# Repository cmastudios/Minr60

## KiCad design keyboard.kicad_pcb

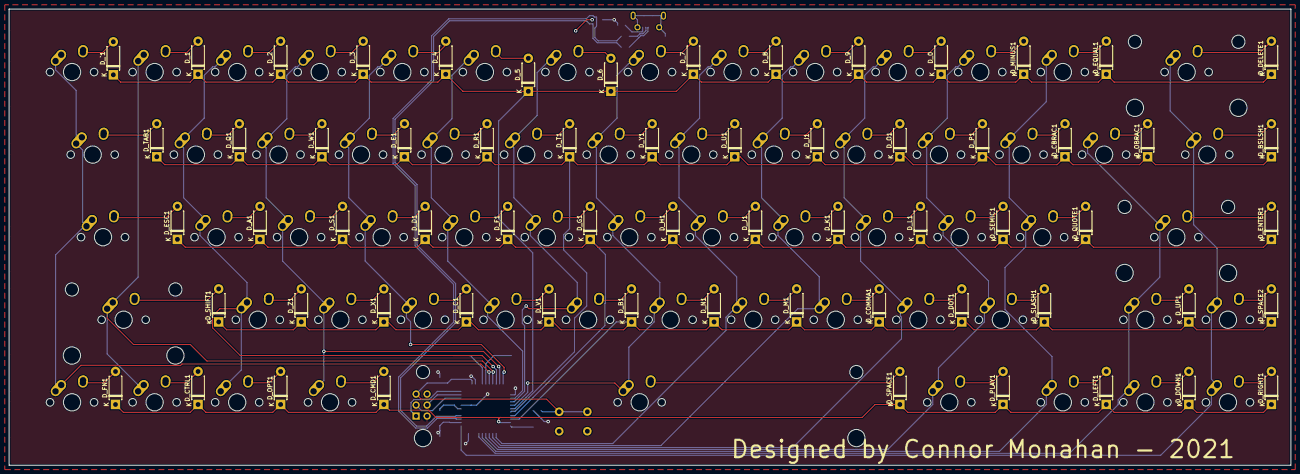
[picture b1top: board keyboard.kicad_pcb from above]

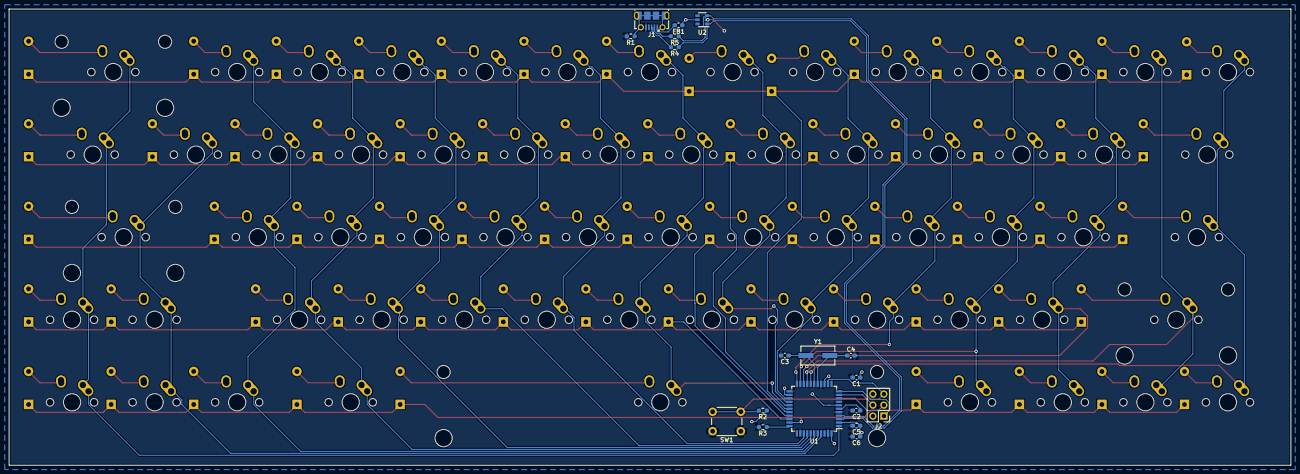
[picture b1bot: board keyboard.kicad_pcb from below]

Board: 2 copper layers, 295.8 x 105.2 mm, 144 parts (18 on the bottom side), 99 nets.

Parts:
C1: 10u; C_0603_1608Metric_Pad1.08x0.95mm_HandSolder
C2, C5: 1u; C_0603_1608Metric_Pad1.08x0.95mm_HandSolder
C3, C4: 22p; C_0603_1608Metric_Pad1.08x0.95mm_HandSolder
C6: 100n; C_0603_1608Metric_Pad1.08x0.95mm_HandSolder
D_0, D_1, D_2, D_3, D_4, D_5, D_6, D_7, D_8, D_9: D; D_DO-41_SOD81_P7.62mm_Horizontal
D_A1: D; D_DO-41_SOD81_P7.62mm_Horizontal
D_B1: D; D_DO-41_SOD81_P7.62mm_Horizontal
D_BSLSH1: D; D_DO-41_SOD81_P7.62mm_Horizontal
D_C1: D; D_DO-41_SOD81_P7.62mm_Horizontal
D_CBRAC1: D; D_DO-41_SOD81_P7.62mm_Horizontal
D_CMD1: D; D_DO-41_SOD81_P7.62mm_Horizontal
D_COMMA1: D; D_DO-41_SOD81_P7.62mm_Horizontal
D_CTRL1: D; D_DO-41_SOD81_P7.62mm_Horizontal
D_D1: D; D_DO-41_SOD81_P7.62mm_Horizontal
D_DELETE1: D; D_DO-41_SOD81_P7.62mm_Horizontal
D_DOT1: D; D_DO-41_SOD81_P7.62mm_Horizontal
D_DOWN1: D; D_DO-41_SOD81_P7.62mm_Horizontal
D_E1: D; D_DO-41_SOD81_P7.62mm_Horizontal
D_ENTER1: D; D_DO-41_SOD81_P7.62mm_Horizontal
D_EQUAL1: D; D_DO-41_SOD81_P7.62mm_Horizontal
D_ESC1: D; D_DO-41_SOD81_P7.62mm_Horizontal
D_F1: D; D_DO-41_SOD81_P7.62mm_Horizontal
D_FN1: D; D_DO-41_SOD81_P7.62mm_Horizontal
D_G1: D; D_DO-41_SOD81_P7.62mm_Horizontal
D_H1: D; D_DO-41_SOD81_P7.62mm_Horizontal
D_I1: D; D_DO-41_SOD81_P7.62mm_Horizontal
D_J1: D; D_DO-41_SOD81_P7.62mm_Horizontal
D_K1: D; D_DO-41_SOD81_P7.62mm_Horizontal
D_L1: D; D_DO-41_SOD81_P7.62mm_Horizontal
D_LEFT1: D; D_DO-41_SOD81_P7.62mm_Horizontal
D_M1: D; D_DO-41_SOD81_P7.62mm_Horizontal
D_MINUS1: D; D_DO-41_SOD81_P7.62mm_Horizontal
D_N1: D; D_DO-41_SOD81_P7.62mm_Horizontal
D_O1: D; D_DO-41_SOD81_P7.62mm_Horizontal
D_OBRAC1: D; D_DO-41_SOD81_P7.62mm_Horizontal
D_OPT1: D; D_DO-41_SOD81_P7.62mm_Horizontal
D_P1: D; D_DO-41_SOD81_P7.62mm_Horizontal
D_PLAY1: D; D_DO-41_SOD81_P7.62mm_Horizontal
D_Q1: D; D_DO-41_SOD81_P7.62mm_Horizontal
D_QUOTE1: D; D_DO-41_SOD81_P7.62mm_Horizontal
D_R1: D; D_DO-41_SOD81_P7.62mm_Horizontal
D_RIGHT1: D; D_DO-41_SOD81_P7.62mm_Horizontal
D_S1: D; D_DO-41_SOD81_P7.62mm_Horizontal
D_SEMIC1: D; D_DO-41_SOD81_P7.62mm_Horizontal
D_SHIFT1: D; D_DO-41_SOD81_P7.62mm_Horizontal
D_SLASH1: D; D_DO-41_SOD81_P7.62mm_Horizontal
D_SPACE1, D_SPACE2: D; D_DO-41_SOD81_P7.62mm_Horizontal
D_T1: D; D_DO-41_SOD81_P7.62mm_Horizontal
D_TAB1: D; D_DO-41_SOD81_P7.62mm_Horizontal
D_U1: D; D_DO-41_SOD81_P7.62mm_Horizontal
D_UP1: D; D_DO-41_SOD81_P7.62mm_Horizontal
D_V1: D; D_DO-41_SOD81_P7.62mm_Horizontal
D_W1: D; D_DO-41_SOD81_P7.62mm_Horizontal
D_X1: D; D_DO-41_SOD81_P7.62mm_Horizontal
D_Y1: D; D_DO-41_SOD81_P7.62mm_Horizontal
D_Z1: D; D_DO-41_SOD81_P7.62mm_Horizontal
D_`1: D; D_DO-41_SOD81_P7.62mm_Horizontal
FB1: Ferrite_Bead_Small; L_0603_1608Metric_Pad1.05x0.95mm_HandSolder
J1: USB_B_Micro; USB_Micro-B_Molex-105017-0001
J2: AVR-ISP-6; PinHeader_2x03_P2.54mm_Vertical
K_0, K_1, K_2, K_3, K_4, K_5, K_6, K_7, K_8, K_9: KEYSW; MX-1U-NoLED
K_A1: KEYSW; MX-1U-NoLED
K_B1: KEYSW; MX-1U-NoLED
K_BSLSH1: KEYSW; MX-1.5U-NoLED
K_C1: KEYSW; MX-1U-NoLED
K_CBRAC1: KEYSW; MX-1U-NoLED
K_CMD1: KEYSW; MX-1.25U-NoLED
K_COMMA1: KEYSW; MX-1U-NoLED
K_CTRL1: KEYSW; MX-1U-NoLED
K_D1: KEYSW; MX-1U-NoLED
K_DELETE1: KEYSW; MX-2U-NoLED
K_DOT1: KEYSW; MX-1U-NoLED
K_DOWN1: KEYSW; MX-1U-NoLED
K_E1: KEYSW; MX-1U-NoLED
K_ENTER1: KEYSW; MX-2.25U-NoLED
K_EQUAL1: KEYSW; MX-1U-NoLED
K_ESC1: KEYSW; MX-1.75U-NoLED
K_F1: KEYSW; MX-1U-NoLED
K_FN1: KEYSW; MX-1U-NoLED
K_G1: KEYSW; MX-1U-NoLED
K_H1: KEYSW; MX-1U-NoLED
K_I1: KEYSW; MX-1U-NoLED
K_J1: KEYSW; MX-1U-NoLED
K_K1: KEYSW; MX-1U-NoLED
K_L1: KEYSW; MX-1U-NoLED
K_LEFT1: KEYSW; MX-1U-NoLED
K_M1: KEYSW; MX-1U-NoLED
K_MINUS1: KEYSW; MX-1U-NoLED
K_N1: KEYSW; MX-1U-NoLED
K_O1: KEYSW; MX-1U-NoLED
K_OBRAC1: KEYSW; MX-1U-NoLED
K_OPT1: KEYSW; MX-1U-NoLED
K_P1: KEYSW; MX-1U-NoLED
K_PLAY1: KEYSW; MX-1.25U-NoLED
K_Q1: KEYSW; MX-1U-NoLED
K_QUOTE1: KEYSW; MX-1U-NoLED
K_R1: KEYSW; MX-1U-NoLED
K_RIGHT1: KEYSW; MX-1U-NoLED
K_S1: KEYSW; MX-1U-NoLED
K_SEMIC1: KEYSW; MX-1U-NoLED
K_SHIFT1: KEYSW; MX-2.25U-NoLED
K_SLASH1: KEYSW; MX-1U-NoLED
K_SPACE1: KEYSW; MX-6.25U-NoLED
K_SPACE2: KEYSW; MX-1U-NoLED
K_T1: KEYSW; MX-1U-NoLED
K_TAB1: KEYSW; MX-1.5U-NoLED
K_U1: KEYSW; MX-1U-NoLED
K_UP1: KEYSW; MX-1U-NoLED
K_V1: KEYSW; MX-1U-NoLED
K_W1: KEYSW; MX-1U-NoLED
K_X1: KEYSW; MX-1U-NoLED
K_Y1: KEYSW; MX-1U-NoLED
K_Z1: KEYSW; MX-1U-NoLED
K_`1: KEYSW; MX-1U-NoLED
R1: 1M; R_0603_1608Metric_Pad0.98x0.95mm_HandSolder
R2, R3: 10k; R_0603_1608Metric_Pad0.98x0.95mm_HandSolder
R4, R5: 22; R_0603_1608Metric_Pad0.98x0.95mm_HandSolder
SW1: SW_Push; SW_PUSH_6mm
U1: ATmega32U4-AU; TQFP-44_10x10mm_P0.8mm
U2: USBLC6-4SC6; SOT-23-6
Y1: 16MHz; Crystal_SMD_ECS_CSM3X-2Pin_7.6x4.1mm

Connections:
/DB+: J1.3, R4.2
/DB-: J1.2, R5.2
D+: R4.1, U1.4, U2.1
D-: R5.1, U1.3, U2.3
GND: C1.2, C2.2, C3.2, C4.2, C5.2, C6.2, J1.5, J2.6, R1.2, R3.2, SW1.1, U1.5, U1.15, U1.23, U1.35, U1.43, U2.2
MISO: J2.1, U1.11
MOSI: J2.4, U1.10
unnamed: C2.1, U1.6
unnamed: C3.1, U1.17, Y1.1
unnamed: C4.1, U1.16, Y1.2
unnamed: D_0.2, K_0.2
unnamed: D_1.2, K_1.2
unnamed: D_2.2, K_2.2
unnamed: D_3.2, K_3.2
unnamed: D_4.2, K_4.2
unnamed: D_5.2, K_5.2
unnamed: D_6.2, K_6.2
unnamed: D_7.2, K_7.2
unnamed: D_8.2, K_8.2
unnamed: D_9.2, K_9.2
unnamed: D_A1.2, K_A1.2
unnamed: D_B1.2, K_B1.2
unnamed: D_BSLSH1.2, K_BSLSH1.2
unnamed: D_C1.2, K_C1.2
unnamed: D_CBRAC1.2, K_CBRAC1.2
unnamed: D_CMD1.2, K_CMD1.2
unnamed: D_COMMA1.2, K_COMMA1.2
unnamed: D_CTRL1.2, K_CTRL1.2
unnamed: D_D1.2, K_D1.2
unnamed: D_DELETE1.2, K_DELETE1.2
unnamed: D_DOT1.2, K_DOT1.2
unnamed: D_DOWN1.2, K_DOWN1.2
unnamed: D_E1.2, K_E1.2
unnamed: D_ENTER1.2, K_ENTER1.2
unnamed: D_EQUAL1.2, K_EQUAL1.2
unnamed: D_ESC1.2, K_ESC1.2
unnamed: D_F1.2, K_F1.2
unnamed: D_FN1.2, K_FN1.2
unnamed: D_G1.2, K_G1.2
unnamed: D_H1.2, K_H1.2
unnamed: D_I1.2, K_I1.2
unnamed: D_J1.2, K_J1.2
unnamed: D_K1.2, K_K1.2
unnamed: D_L1.2, K_L1.2
unnamed: D_LEFT1.2, K_LEFT1.2
unnamed: D_M1.2, K_M1.2
unnamed: D_MINUS1.2, K_MINUS1.2
unnamed: D_N1.2, K_N1.2
unnamed: D_O1.2, K_O1.2
unnamed: D_OBRAC1.2, K_OBRAC1.2
unnamed: D_OPT1.2, K_OPT1.2
unnamed: D_P1.2, K_P1.2
unnamed: D_PLAY1.2, K_PLAY1.2
unnamed: D_Q1.2, K_Q1.2
unnamed: D_QUOTE1.2, K_QUOTE1.2
unnamed: D_R1.2, K_R1.2
unnamed: D_RIGHT1.2, K_RIGHT1.2
unnamed: D_S1.2, K_S1.2
unnamed: D_SEMIC1.2, K_SEMIC1.2
unnamed: D_SHIFT1.2, K_SHIFT1.2
unnamed: D_SLASH1.2, K_SLASH1.2
unnamed: D_SPACE1.2, K_SPACE1.2
unnamed: D_SPACE2.2, K_SPACE2.2
unnamed: D_T1.2, K_T1.2
unnamed: D_TAB1.2, K_TAB1.2
unnamed: D_U1.2, K_U1.2
unnamed: D_UP1.2, K_UP1.2
unnamed: D_V1.2, K_V1.2
unnamed: D_W1.2, K_W1.2
unnamed: D_X1.2, K_X1.2
unnamed: D_Y1.2, K_Y1.2
unnamed: D_Z1.2, K_Z1.2
unnamed: D_`1.2, K_`1.2
unnamed: FB1.2, J1.1
unnamed: J1.6, R1.1
unnamed: R3.1, U1.33
RST: J2.5, R2.2, SW1.2, U1.13
SCK: J2.3, U1.9
VCC: C1.1, C5.1, C6.1, FB1.1, J2.2, R2.1, U1.2, U1.7, U1.14, U1.24, U1.34, U1.44, U2.5
col0: K_ESC1.1, K_FN1.1, K_TAB1.1, K_`1.1, U1.18
col1: K_1.1, K_CTRL1.1, K_SHIFT1.1, U1.19
col2: K_2.1, K_A1.1, K_OPT1.1, K_Q1.1, K_Z1.1, U1.20
col3: K_3.1, K_CMD1.1, K_S1.1, K_W1.1, K_X1.1, U1.21
col4: K_4.1, K_C1.1, K_D1.1, K_E1.1, U1.22
col5: K_5.1, K_F1.1, K_R1.1, K_V1.1, U1.25
col6: K_6.1, K_B1.1, K_G1.1, K_T1.1, U1.26
col7: K_7.1, K_H1.1, K_N1.1, K_SPACE1.1, K_Y1.1, U1.27
col8: K_8.1, K_J1.1, K_M1.1, K_U1.1, U1.36
col9: K_9.1, K_COMMA1.1, K_I1.1, K_K1.1, U1.37
col10: K_0.1, K_DOT1.1, K_L1.1, K_O1.1, U1.38
col11: K_MINUS1.1, K_P1.1, K_PLAY1.1, K_SEMIC1.1, K_SLASH1.1, U1.39
col12: K_CBRAC1.1, K_EQUAL1.1, K_LEFT1.1, K_QUOTE1.1, U1.40
col13: K_DOWN1.1, K_ENTER1.1, K_OBRAC1.1, K_UP1.1, U1.41
col14: K_BSLSH1.1, K_DELETE1.1, K_RIGHT1.1, K_SPACE2.1, U1.1
row0: D_0.1, D_1.1, D_2.1, D_3.1, D_4.1, D_5.1, D_6.1, D_7.1, D_8.1, D_9.1, D_DELETE1.1, D_EQUAL1.1, D_MINUS1.1, D_`1.1, U1.28
row1: D_BSLSH1.1, D_CBRAC1.1, D_E1.1, D_I1.1, D_O1.1, D_OBRAC1.1, D_P1.1, D_Q1.1, D_R1.1, D_T1.1, D_TAB1.1, D_U1.1, D_W1.1, D_Y1.1, U1.29
row2: D_A1.1, D_D1.1, D_ENTER1.1, D_ESC1.1, D_F1.1, D_G1.1, D_H1.1, D_J1.1, D_K1.1, D_L1.1, D_QUOTE1.1, D_S1.1, D_SEMIC1.1, U1.30
row3: D_B1.1, D_C1.1, D_COMMA1.1, D_DOT1.1, D_M1.1, D_N1.1, D_SHIFT1.1, D_SLASH1.1, D_SPACE2.1, D_UP1.1, D_V1.1, D_X1.1, D_Z1.1, U1.31
row4: D_CMD1.1, D_CTRL1.1, D_DOWN1.1, D_FN1.1, D_LEFT1.1, D_OPT1.1, D_PLAY1.1, D_RIGHT1.1, D_SPACE1.1, U1.32
